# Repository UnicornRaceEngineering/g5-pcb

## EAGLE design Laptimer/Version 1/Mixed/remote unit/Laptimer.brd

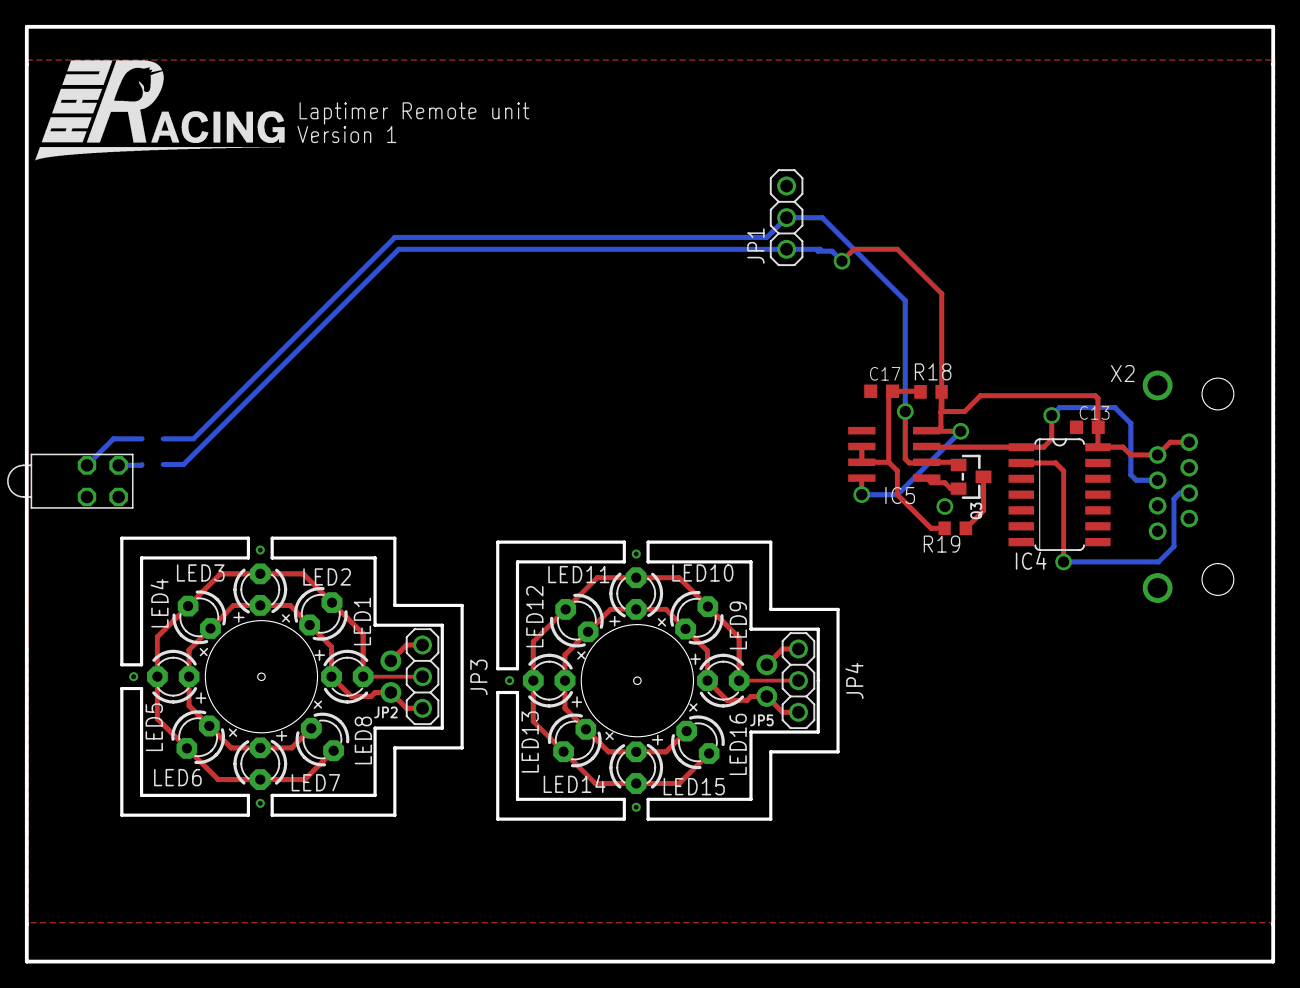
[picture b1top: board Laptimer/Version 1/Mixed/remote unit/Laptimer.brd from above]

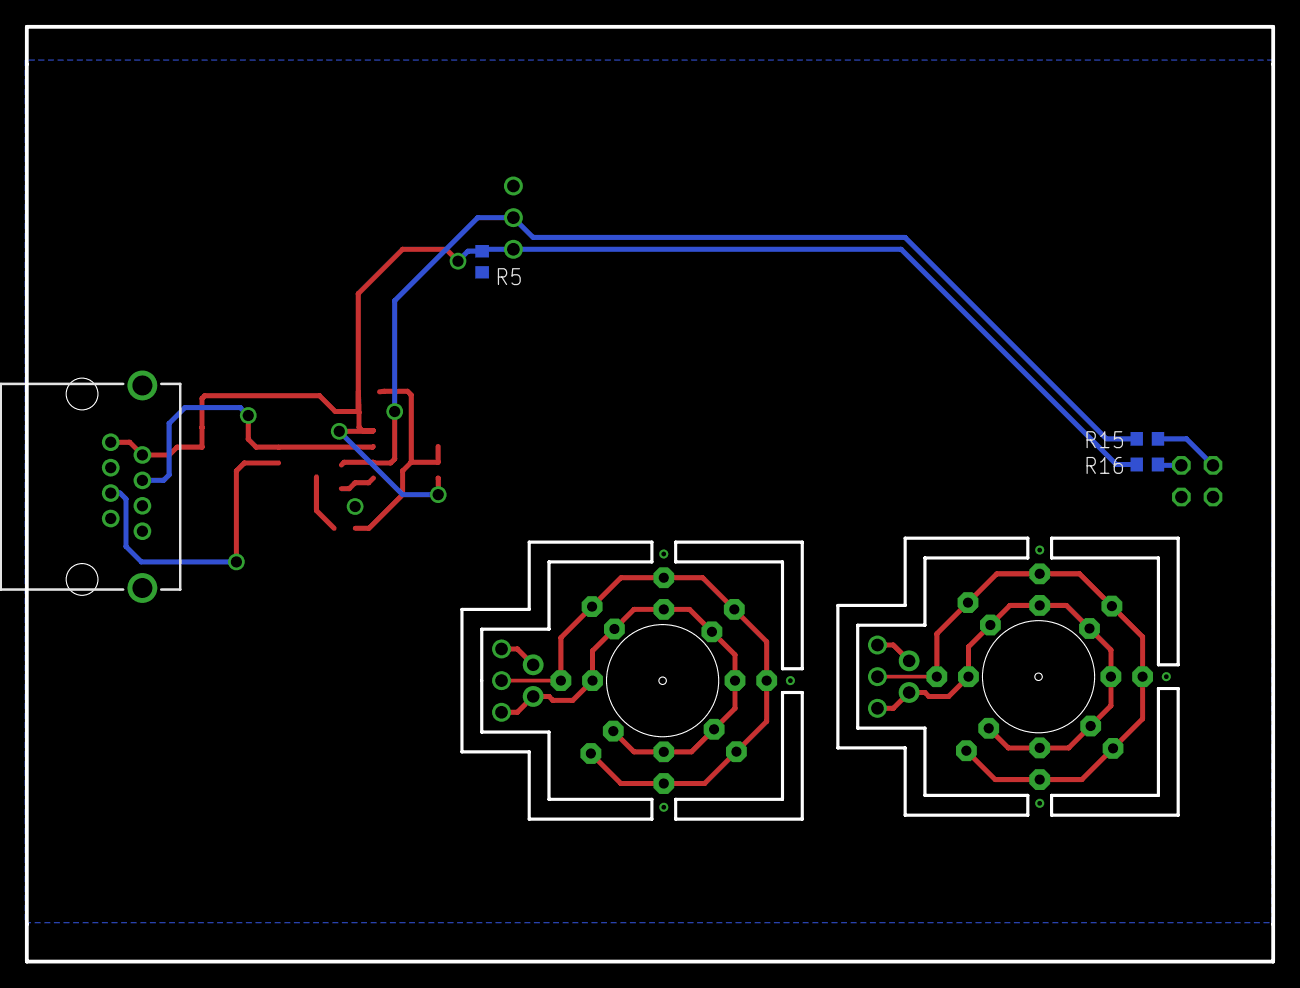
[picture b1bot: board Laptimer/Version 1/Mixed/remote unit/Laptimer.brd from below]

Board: 2 copper layers, 100.0 x 75.0 mm, 33 parts (3 on the bottom side), 15 nets.

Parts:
C13, C17: 100n; C0603K
IC4: 74HC04D; SO14
IC5: NE555D; SO08
JP1, JP3, JP4: 1X03
JP2, JP5: 1X02_ROUND
LED1, LED2, LED3, LED4, LED5, LED6, LED7, LED8, LED9, LED10, LED11, LED12, LED13, LED14, LED15, LED16: SFH 309; LED3MM
Q3: SOT23-WIDE
R5, R18: 1k; R0603
R15, R16: 220; R0603
R19: 100; R0603
U$19: BI-LEVEL-LED-INDICATOR
X2: GLX-S-88M

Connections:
5.0V: C13.2, IC4.14, IC5.4, IC5.8, JP1.1, R5.1, R16.1, R18.1, X2.1, X2.2
GND: C13.1, C17.2, IC4.3, IC4.5, IC4.7, IC4.9, IC4.11, IC4.13, IC5.1, JP1.3, Q3.2, R5.2, U$19.CATHODE1, U$19.CATHODE2, X2.3, X2.6, X2.7, X2.8, X2.S1, X2.S2
INT: JP3.2, LED1.K, LED2.K, LED3.K, LED4.K, LED5.K, LED6.K, LED7.K, LED8.K
INT1: JP4.2, LED9.K, LED10.K, LED11.K, LED12.K, LED13.K, LED14.K, LED15.K, LED16.K
unnamed: JP4.1, JP5.1
unnamed: JP4.3, JP5.2, LED9.A, LED10.A, LED11.A, LED12.A, LED13.A, LED14.A, LED15.A, LED16.A
unnamed: JP2.1, JP3.1
unnamed: IC4.2, X2.5
unnamed: R15.2, U$19.ANODE1
unnamed: R16.2, U$19.ANODE2
unnamed: C17.1, IC5.6, IC5.7, R18.2, R19.2
unnamed: JP2.2, JP3.3, LED1.A, LED2.A, LED3.A, LED4.A, LED5.A, LED6.A, LED7.A, LED8.A
unnamed: Q3.3, R19.1
PT-IN: IC5.2, JP1.2, Q3.1, R15.1
PT-OUT: IC4.1, IC5.3, X2.4

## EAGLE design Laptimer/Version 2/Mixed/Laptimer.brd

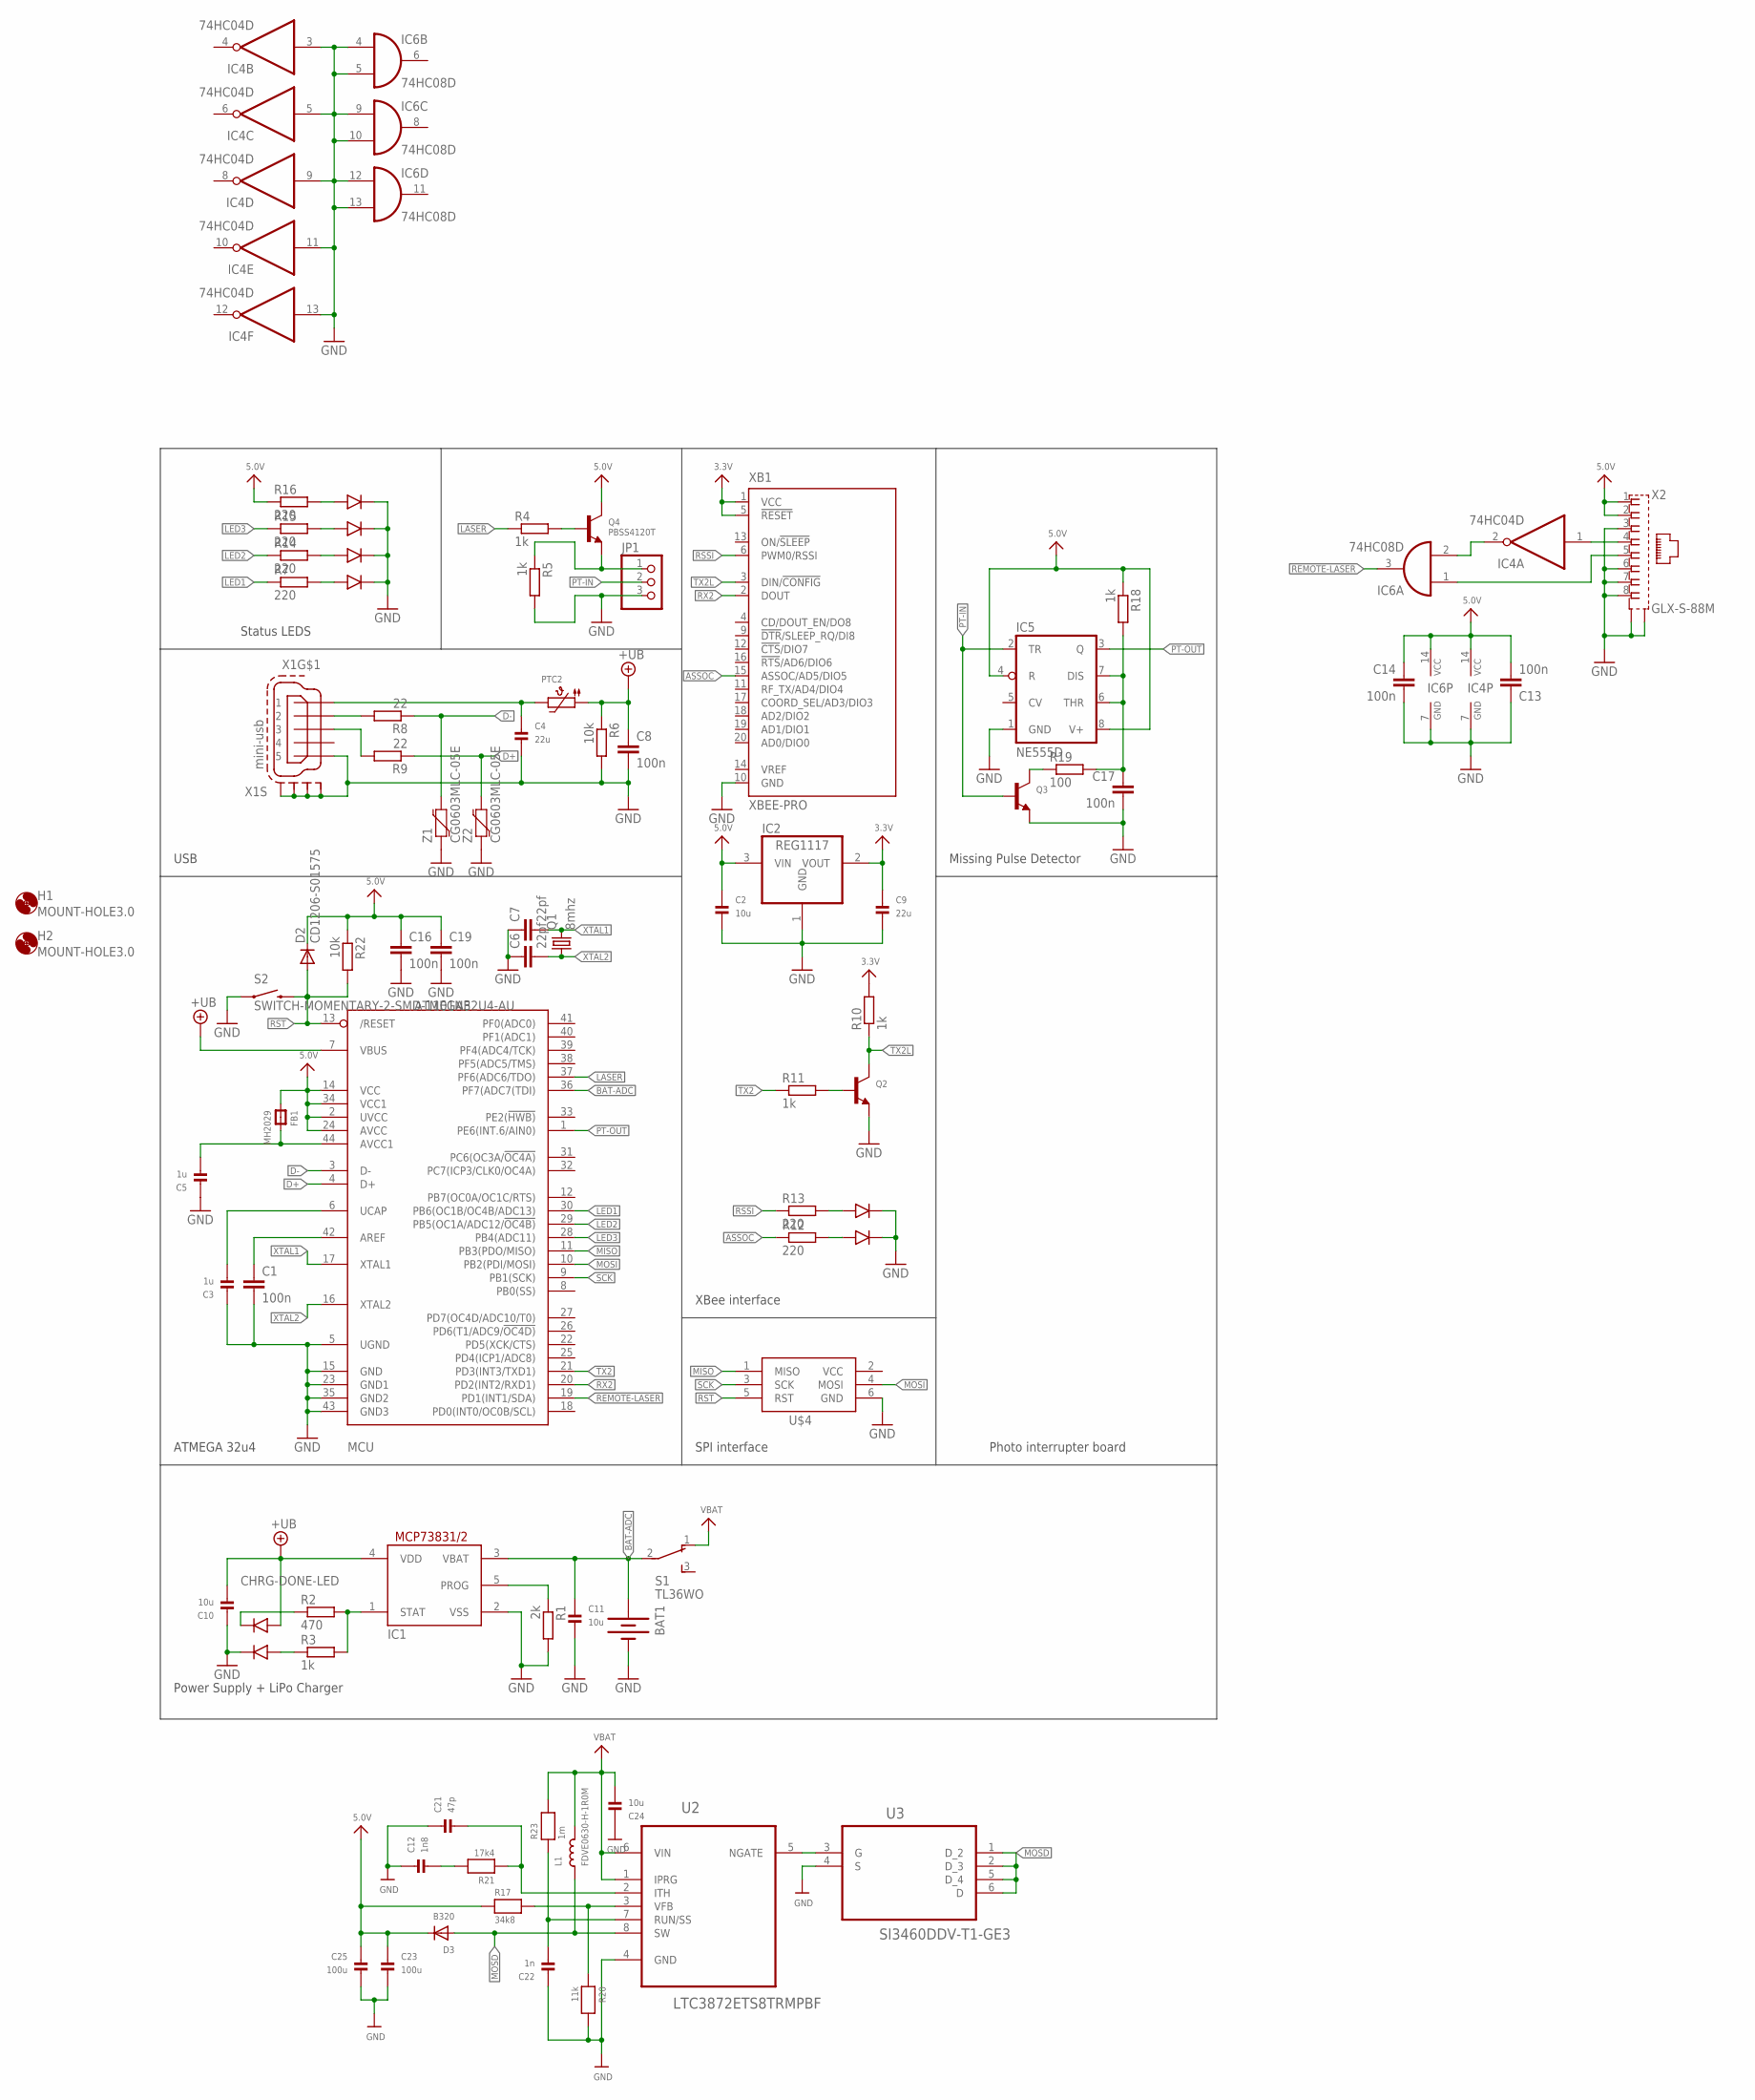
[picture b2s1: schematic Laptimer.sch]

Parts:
BAT1: BATTERY18650; BATTERY_18650-HOLDER
C1, C8, C13, C14, C16, C17, C19: 100n; C0603K
C2, C24: 10u; _0805
C3, C5: 1u; _0805MP
C4: 22u; _0805MP
C6, C7: 22pf; C0603K
C9: 22u; _0805
C10, C11: 10u; _0805MP
C12: 1n8; _0603
C21: 47p; _0603
C22: 1n; _0603
C23, C25: 100u; 1206
D2: CD1206-S01575; MINIMELF
D3: B320; SMADIODE
FB1: MH2029; _0805MP
H1, H2: MOUNT-HOLE3.0; 3,0
IC1: MCP73831/OT; SOT23-5L
IC2: REG1117; SOT223
IC4: 74HC04D; SO14
IC5: NE555D; SO08
IC6: 74HC08D; SO14
JP1: PINHD-1X3; 1X03
L1: FDVE0630-H-1R0M; INDUCTOR_6X6MM_TDK_SLF6045
MCU: ATMEGA32U4-AU; TQFP44
PTC2: PTC1206; 1206
Q1: 8mhz; HC49/S
Q2, Q3: TRANSISTOR_NPNWIDE; SOT23-WIDE
Q4: PBSS4120T; SOT23-WIDE
R1: 2k; R0603
R2: 470; R0603
R3, R4, R5, R10, R11, R18: 1k; R0603
R6, R22: 10k; R0603
R7, R12, R13, R14, R15, R16: 220; R0603
R8, R9: 22; R0603
R17: 34k8; _0603
R19: 100; R0603
R20: 11k; _0603
R21: 17k4; _0603
R23: 1m; _0603
S1: TL36WO; TL3XWO
S2: SWITCH-MOMENTARY-2-SMD-1101NE; TACTILE-SWITCH-1101NE
U2: LTC3872ETS8TRMPBF; SOT65P280X100-8N
U3: SI3460DDV-T1-GE3; SOT95P285X110-6N
U$1, U$11, U$18, U$19: BI-LEVEL-LED-INDICATOR
U$4: AVRISP-BOX
X1: mini-usb; 32005-301
X2: GLX-S-88M
XB1: XBEE-PRO
Z1, Z2: CG0603MLC-05E; 0603-RES

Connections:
1D+: R9.2, X1.3
1D-: R8.2, X1.2
3.3V: C9.1, IC2.2 (VOUT), R10.2, XB1.1 (VCC), XB1.5 (!RESET)
5.0V: C2.1, C13.2, C14.1, C16.1, C19.1, C23.1, C25.1, D2.C, D3.C, FB1.1, IC2.3 (VIN), IC4.14 (VCC), IC5.4 (R), IC5.8 (V+), IC6.14 (VCC), MCU.2 (UVCC), MCU.14 (VCC), MCU.24 (AVCC), MCU.34 (VCC1), Q4.3 (C), R16.1, R17.1, R18.1, R22.1, X2.1, X2.2
+UB: C8.1, C10.2, IC1.4 (VDD), MCU.7 (VBUS), PTC2.1, R6.1, U$1.ANODE1
ASSOC: R12.1, XB1.15 (ASSOC/AD5/DIO5)
BAT-ADC: BAT1.PWR@1 (+), C11.1, IC1.3 (VBAT), MCU.36 (PF7(ADC7(TDI)), S1.2
CHRG-DONE-LED: R3.1, U$1.ANODE2
D+: MCU.4 (D+), R9.1, Z2.2
D-: MCU.3 (D-), R8.1, Z1.2
GND: BAT1.GND@1 (-), C1.2, C2.2, C3.1, C4.2, C5.1, C6.1, C7.1, C8.2, C9.2, C10.1, C11.2, C12.1, C13.1, C14.2, C16.2, C17.2, C19.2, C21.1, C22.1, C23.2, C24.1, C25.2, IC1.2 (VSS), IC2.1 (GND), IC4.3 (I), IC4.5 (I), IC4.7 (GND), IC4.9 (I), IC4.11 (I), IC4.13 (I), IC5.1 (GND), IC6.4 (I0), IC6.5 (I1), IC6.7 (GND), IC6.9 (I0), IC6.10 (I1), IC6.12 (I0), IC6.13 (I1), JP1.3, MCU.5 (UGND), MCU.15 (GND), MCU.23 (GND1), MCU.35 (GND2), MCU.43 (GND3), Q2.2 (E), Q3.2 (E), R1.2, R5.2, R6.2, R20.2, S2.P$1 (1), U2.4 (GND), U3.4 (S), U$1.CATHODE2, U$4.6 (GND), U$11.CATHODE1, U$11.CATHODE2, U$18.CATHODE1, U$18.CATHODE2, U$19.CATHODE1, U$19.CATHODE2, X1.5, X1.M1 (S1), X1.M2 (S2), X1.M3 (S3), X1.M4 (S4), X2.3, X2.6, X2.7, X2.8, X2.S1, X2.S2, XB1.10 (GND), Z1.1, Z2.1
LASER: MCU.37 (PF6(ADC6/TDO)), R4.1
LED1: MCU.30 (PB6(OC1B/OC4B/ADC13)), R7.1
LED2: MCU.29 (PB5(OC1A/ADC12/!OC4B)), R14.1
LED3: MCU.28 (PB4(ADC11)), R15.1
MISO: MCU.11 (PB3(PDO/MISO)), U$4.1 (MISO)
MOSD: D3.A, L1.P$1 (1), U2.8 (SW), U3.1 (D_2), U3.2 (D_3), U3.5 (D_4), U3.6 (D)
MOSI: MCU.10 (PB2(PDI/MOSI)), U$4.4 (MOSI)
unnamed: R17.2, R20.1, U2.3 (VFB)
unnamed: C12.2, R21.2
unnamed: IC1.5 (PROG), R1.1
unnamed: IC1.1 (STAT), R2.2, R3.2
unnamed: JP1.1, Q4.2 (E), R5.1
unnamed: Q4.1 (B), R4.2
unnamed: C5.2, FB1.2, MCU.44 (AVCC1)
unnamed: U2.5 (NGATE), U3.3 (G)
unnamed: C1.1, MCU.42 (AREF)
unnamed: C3.2, MCU.6 (UCAP)
unnamed: C4.1, PTC2.2, X1.1
unnamed: R2.1, U$1.CATHODE1
unnamed: R7.2, U$18.ANODE1
unnamed: R12.2, U$11.ANODE1
unnamed: Q2.1 (B), R11.2
unnamed: R13.2, U$11.ANODE2
unnamed: IC4.1 (I), X2.4
unnamed: R14.2, U$18.ANODE2
unnamed: IC6.1 (I0), X2.5
unnamed: R15.2, U$19.ANODE1
unnamed: C21.2, R21.1, U2.2 (ITH)
unnamed: IC4.2 (O), IC6.2 (I1)
unnamed: C22.2, R23.1, U2.7 (RUN/SS)
unnamed: R16.2, U$19.ANODE2
unnamed: C17.1, IC5.6 (THR), IC5.7 (DIS), R18.2, R19.2
unnamed: Q3.3 (C), R19.1
PT-IN: IC5.2 (TR), JP1.2, Q3.1 (B)
PT-OUT: IC5.3 (Q), MCU.1 (PE6(INT.6/AIN0))
REMOTE-LASER: IC6.3 (O), MCU.19 (PD1(INT1/SDA))
RSSI: R13.1, XB1.6 (PWM0/RSSI)
RST: D2.A, MCU.13 (/RESET), R22.2, S2.P$2 (2), U$4.5 (RST)
RX2: MCU.20 (PD2(INT2/RXD1)), XB1.2 (DOUT)
SCK: MCU.9 (PB1(SCK)), U$4.3 (SCK)
TX2: MCU.21 (PD3(INT3/TXD1)), R11.1
TX2L: Q2.3 (C), R10.1, XB1.3 (DIN/!CONFIG)
VBAT: C24.2, L1.P$2 (2), R23.2, S1.1 (O), U2.1 (IPRG), U2.6 (VIN)
VCC: U$4.2 (VCC)
XTAL1: C7.2, MCU.17 (XTAL1), Q1.2
XTAL2: C6.2, MCU.16 (XTAL2), Q1.1

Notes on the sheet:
Power Supply + LiPo Charger
ATMEGA 32u4
USB
Status LEDS
XBee interface
Missing Pulse Detector
Photo interrupter board
SPI interface

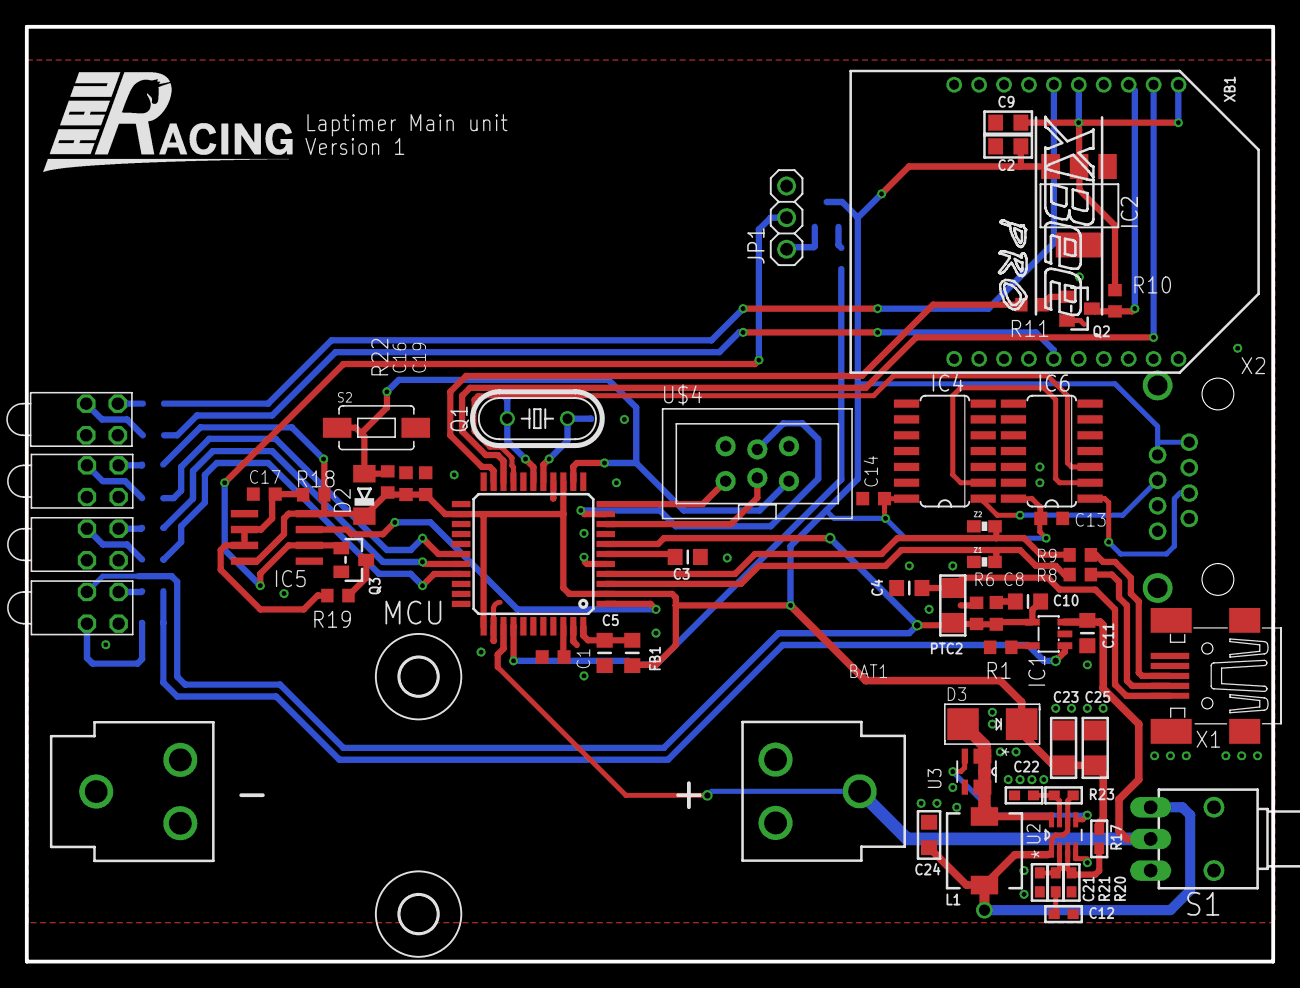
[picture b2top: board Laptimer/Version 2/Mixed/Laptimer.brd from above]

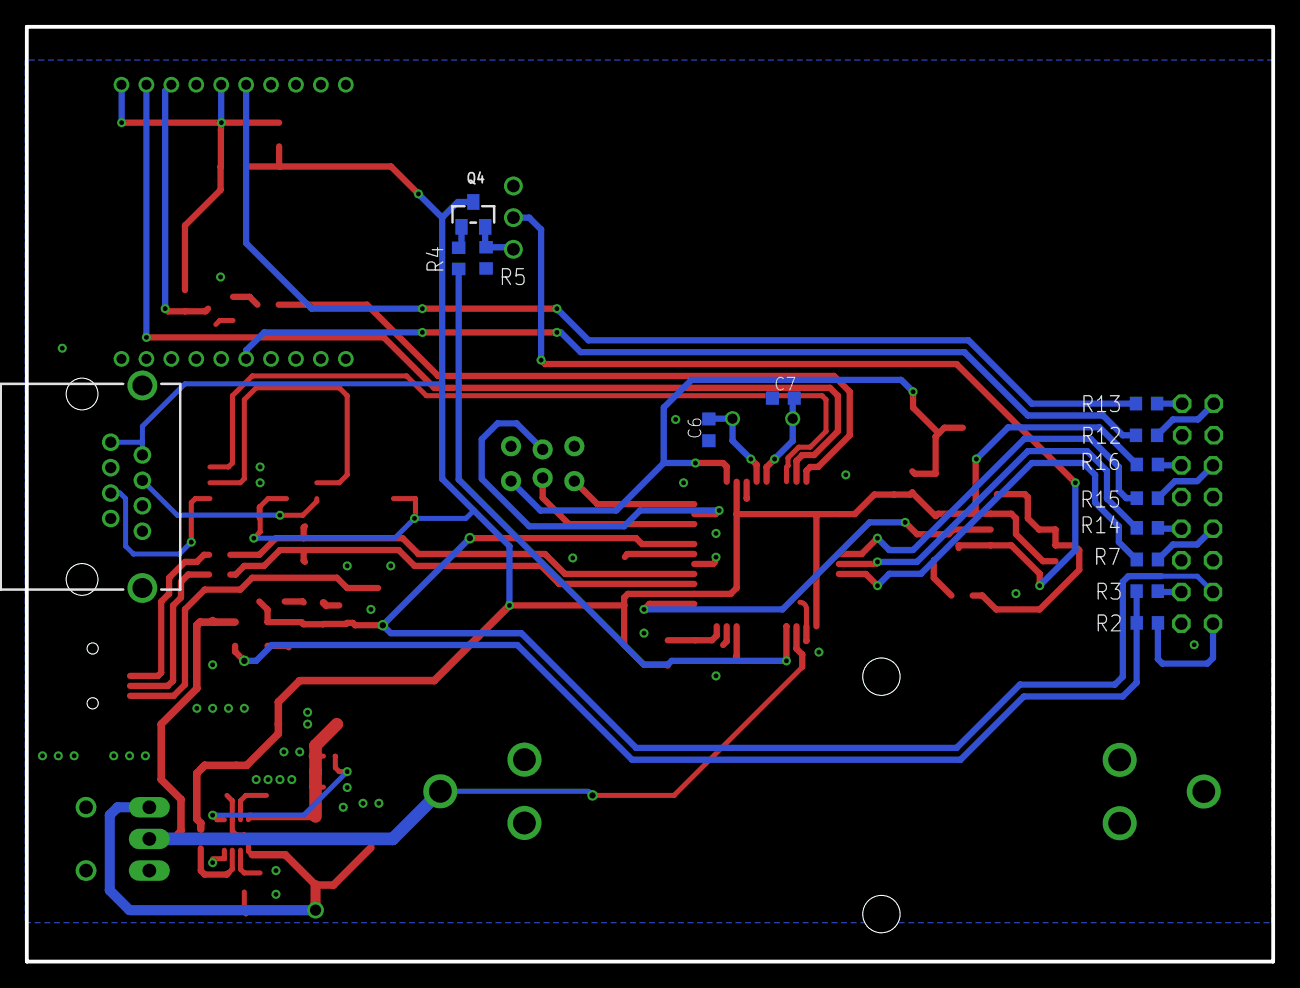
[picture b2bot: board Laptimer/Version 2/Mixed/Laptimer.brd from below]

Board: 2 copper layers, 100.0 x 75.0 mm, 78 parts (13 on the bottom side), 56 nets.

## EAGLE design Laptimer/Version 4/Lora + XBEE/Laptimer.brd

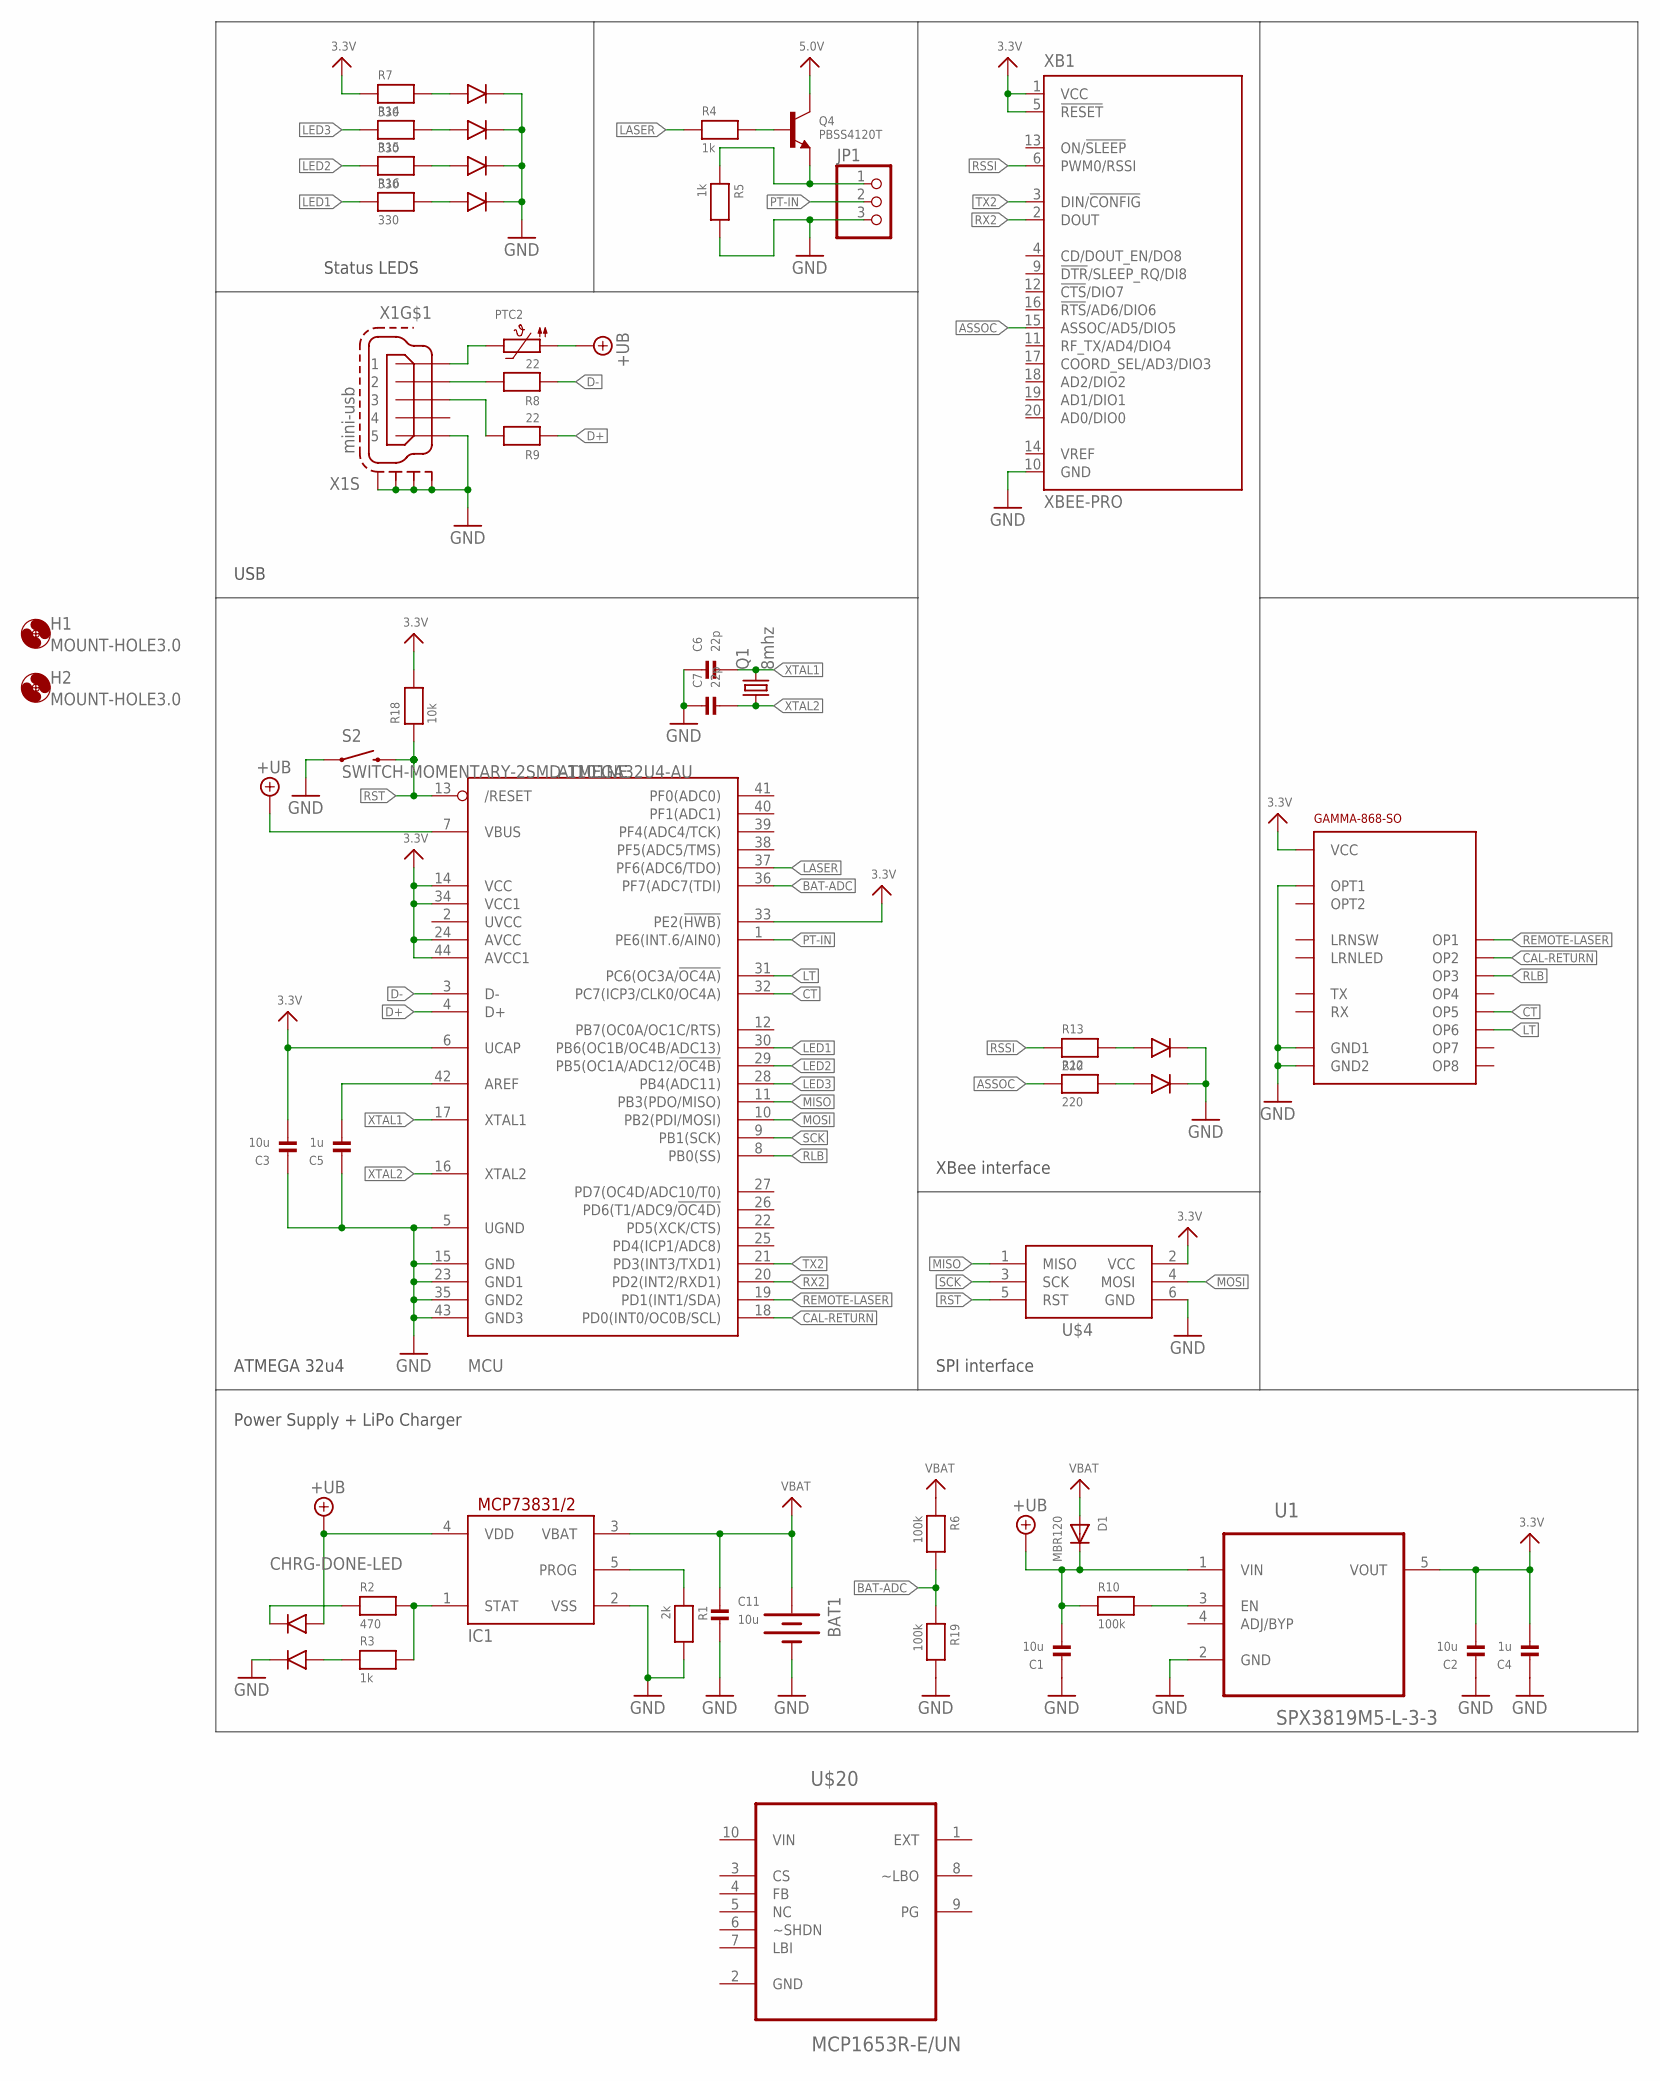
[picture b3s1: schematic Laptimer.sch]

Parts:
BAT1: BATTERY18650; BATTERY_18650-HOLDER
C1, C2, C3, C11: 10u; _0805
C4, C5: 1u; _0805
C6, C7: 22p; _0603
D1: MBR120; SOD-123
H1, H2: MOUNT-HOLE3.0; 3,0
IC1: MCP73831/OT; SOT23-5L
JP1: PINHD-1X3; 1X03
MCU: ATMEGA32U4-AU; TQFP44
PTC2: PTC1206; 1206
Q1: 8mhz; HC49/S
Q4: PBSS4120T; SOT23-WIDE
R1: 2k; _0603
R2: 470; _0603
R3, R4, R5: 1k; _0603
R6, R10, R19: 100k; _0603
R7, R14, R15, R16: 330; _0603
R8, R9: 22; _0603
R12, R13: 220; _0603
R18: 10k; _0603
S2: SWITCH-MOMENTARY-2SMD-1101NE; TACTILE-SWITCH-1101NE
U1: SPX3819M5-L-3-3; SOT95P280X145-5N
U$4: AVRISP-BOX
U$7: GAMMA-868-SO; UNICORN_V2_GAMMA-868-SO
U$11, U$13, U$14, U$17: BI-LEVEL-LED-INDICATOR
U$20: MCP1653R-E/UN; SOP50P490X110-10N
X1: mini-usb; 32005-301
XB1: XBEE-PRO

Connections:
1D+: R9.2, X1.3
1D-: R8.2, X1.2
3.3V: C2.2, C3.2, C4.2, MCU.6 (UCAP), MCU.14 (VCC), MCU.24 (AVCC), MCU.33 (PE2(!HWB)), MCU.34 (VCC1), MCU.44 (AVCC1), R7.1, R18.2, U1.5 (VOUT), U$4.2 (VCC), U$7.P$16 (VCC), XB1.1 (VCC), XB1.5 (!RESET)
5.0V: Q4.3 (C)
+UB: C1.2, D1.C, IC1.4 (VDD), MCU.7 (VBUS), PTC2.1, R10.1, U1.1 (VIN), U$13.ANODE1
ASSOC: R12.1, XB1.15 (ASSOC/AD5/DIO5)
BAT-ADC: MCU.36 (PF7(ADC7(TDI)), R6.2, R19.1
CAL-RETURN: MCU.18 (PD0(INT0/OC0B/SCL)), U$7.P$4 (OP2)
CHRG-DONE-LED: R3.1, U$13.ANODE2
CT: MCU.32 (PC7(ICP3/CLK0/OC4A)), U$7.P$9 (OP5)
D+: MCU.4 (D+), R9.1
D-: MCU.3 (D-), R8.1
GND: BAT1.GND@1 (-), C1.1, C2.1, C3.1, C4.1, C5.1, C6.1, C7.1, C11.2, IC1.2 (VSS), JP1.3, MCU.5 (UGND), MCU.15 (GND), MCU.23 (GND1), MCU.35 (GND2), MCU.43 (GND3), R1.2, R5.2, R19.2, S2.1, U1.2 (GND), U$4.6 (GND), U$7.P$2 (GND1), U$7.P$10 (OPT1), U$7.P$15 (GND2), U$11.CATHODE1, U$11.CATHODE2, U$13.CATHODE2, U$14.CATHODE1, U$14.CATHODE2, U$17.CATHODE1, U$17.CATHODE2, X1.5, X1.M1 (S1), X1.M2 (S2), X1.M3 (S3), X1.M4 (S4), XB1.10 (GND)
LASER: MCU.37 (PF6(ADC6/TDO)), R4.1
LED1: MCU.30 (PB6(OC1B/OC4B/ADC13)), R16.1
LED2: MCU.29 (PB5(OC1A/ADC12/!OC4B)), R15.1
LED3: MCU.28 (PB4(ADC11)), R14.1
LT: MCU.31 (PC6(OC3A/!OC4A)), U$7.P$11 (OP6)
MISO: MCU.11 (PB3(PDO/MISO)), U$4.1 (MISO)
MOSI: MCU.10 (PB2(PDI/MOSI)), U$4.4 (MOSI)
unnamed: R10.2, U1.3 (EN)
unnamed: IC1.5 (PROG), R1.1
unnamed: IC1.1 (STAT), R2.2, R3.2
unnamed: JP1.1, Q4.2 (E), R5.1
unnamed: Q4.1 (B), R4.2
unnamed: C5.2, MCU.42 (AREF)
unnamed: PTC2.2, X1.1
unnamed: R2.1, U$13.CATHODE1
unnamed: R16.2, U$17.ANODE1
unnamed: R12.2, U$11.ANODE1
unnamed: R13.2, U$11.ANODE2
unnamed: R15.2, U$17.ANODE2
unnamed: R14.2, U$14.ANODE1
unnamed: R7.2, U$14.ANODE2
PT-IN: JP1.2, MCU.1 (PE6(INT.6/AIN0))
REMOTE-LASER: MCU.19 (PD1(INT1/SDA)), U$7.P$3 (OP1)
RLB: MCU.8 (PB0(SS)), U$7.P$7 (OP3)
RSSI: R13.1, XB1.6 (PWM0/RSSI)
RST: MCU.13 (/RESET), R18.1, S2.2, U$4.5 (RST)
RX2: MCU.20 (PD2(INT2/RXD1)), XB1.2 (DOUT)
SCK: MCU.9 (PB1(SCK)), U$4.3 (SCK)
TX2: MCU.21 (PD3(INT3/TXD1)), XB1.3 (DIN/!CONFIG)
VBAT: BAT1.PWR@1 (+), C11.1, D1.A, IC1.3 (VBAT), R6.1
VIN: U$20.10 (VIN)
XTAL1: C6.2, MCU.17 (XTAL1), Q1.2
XTAL2: C7.2, MCU.16 (XTAL2), Q1.1

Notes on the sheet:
Power Supply + LiPo Charger
ATMEGA 32u4
USB
Status LEDS
XBee interface
SPI interface

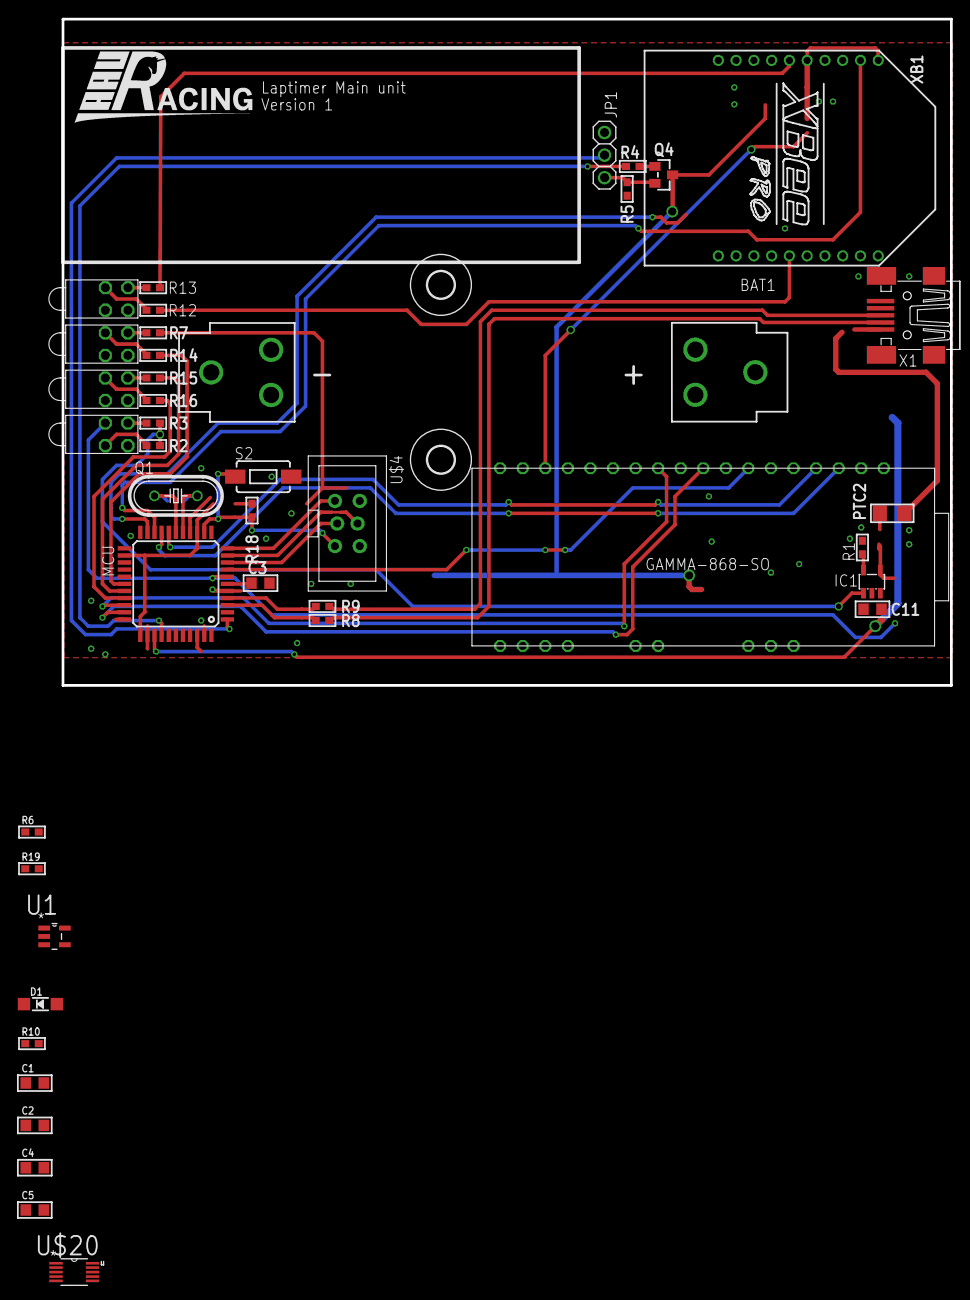
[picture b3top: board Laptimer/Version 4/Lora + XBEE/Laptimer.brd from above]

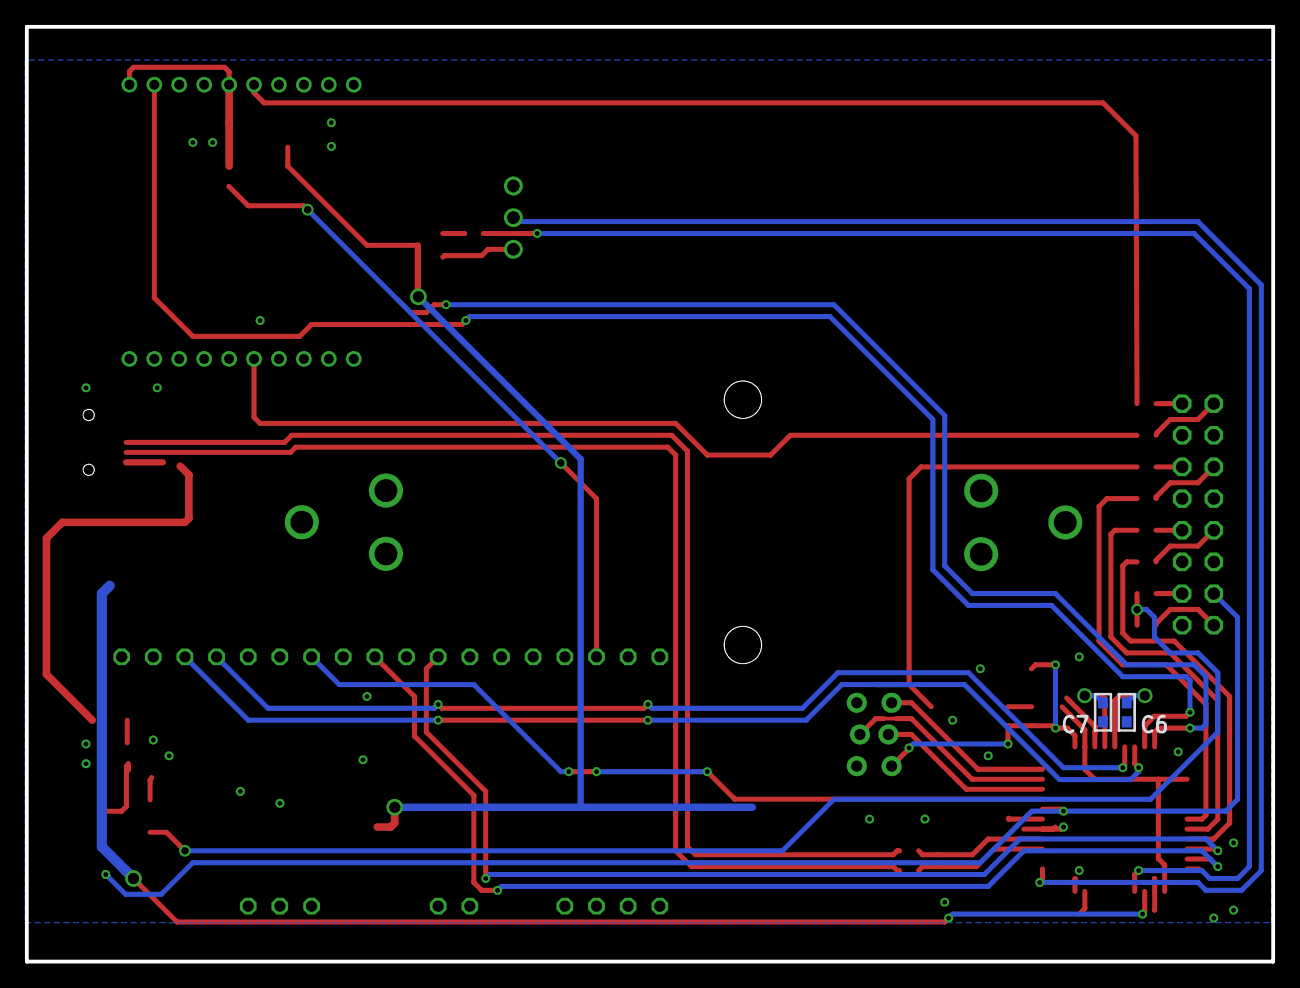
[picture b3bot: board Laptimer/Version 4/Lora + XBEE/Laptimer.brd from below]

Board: 2 copper layers, 100.0 x 75.0 mm, 46 parts (2 on the bottom side), 44 nets.

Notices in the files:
parts and their libraries:
microbuilder: This work is placed in the public domain, and may be freely used for commercial and non-commercial work with the following conditions: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
SparkFun-Electromechanical: Licensing: Creative Commons ShareAlike 4.0 International - https://creativecommons.org/licenses/by-sa/4.0
